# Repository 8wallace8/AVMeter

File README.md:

"# AVMeter"

Versiion 1.2 fixes input order for LM6105.  Also adds negative voltage supply directly from PSU's board.

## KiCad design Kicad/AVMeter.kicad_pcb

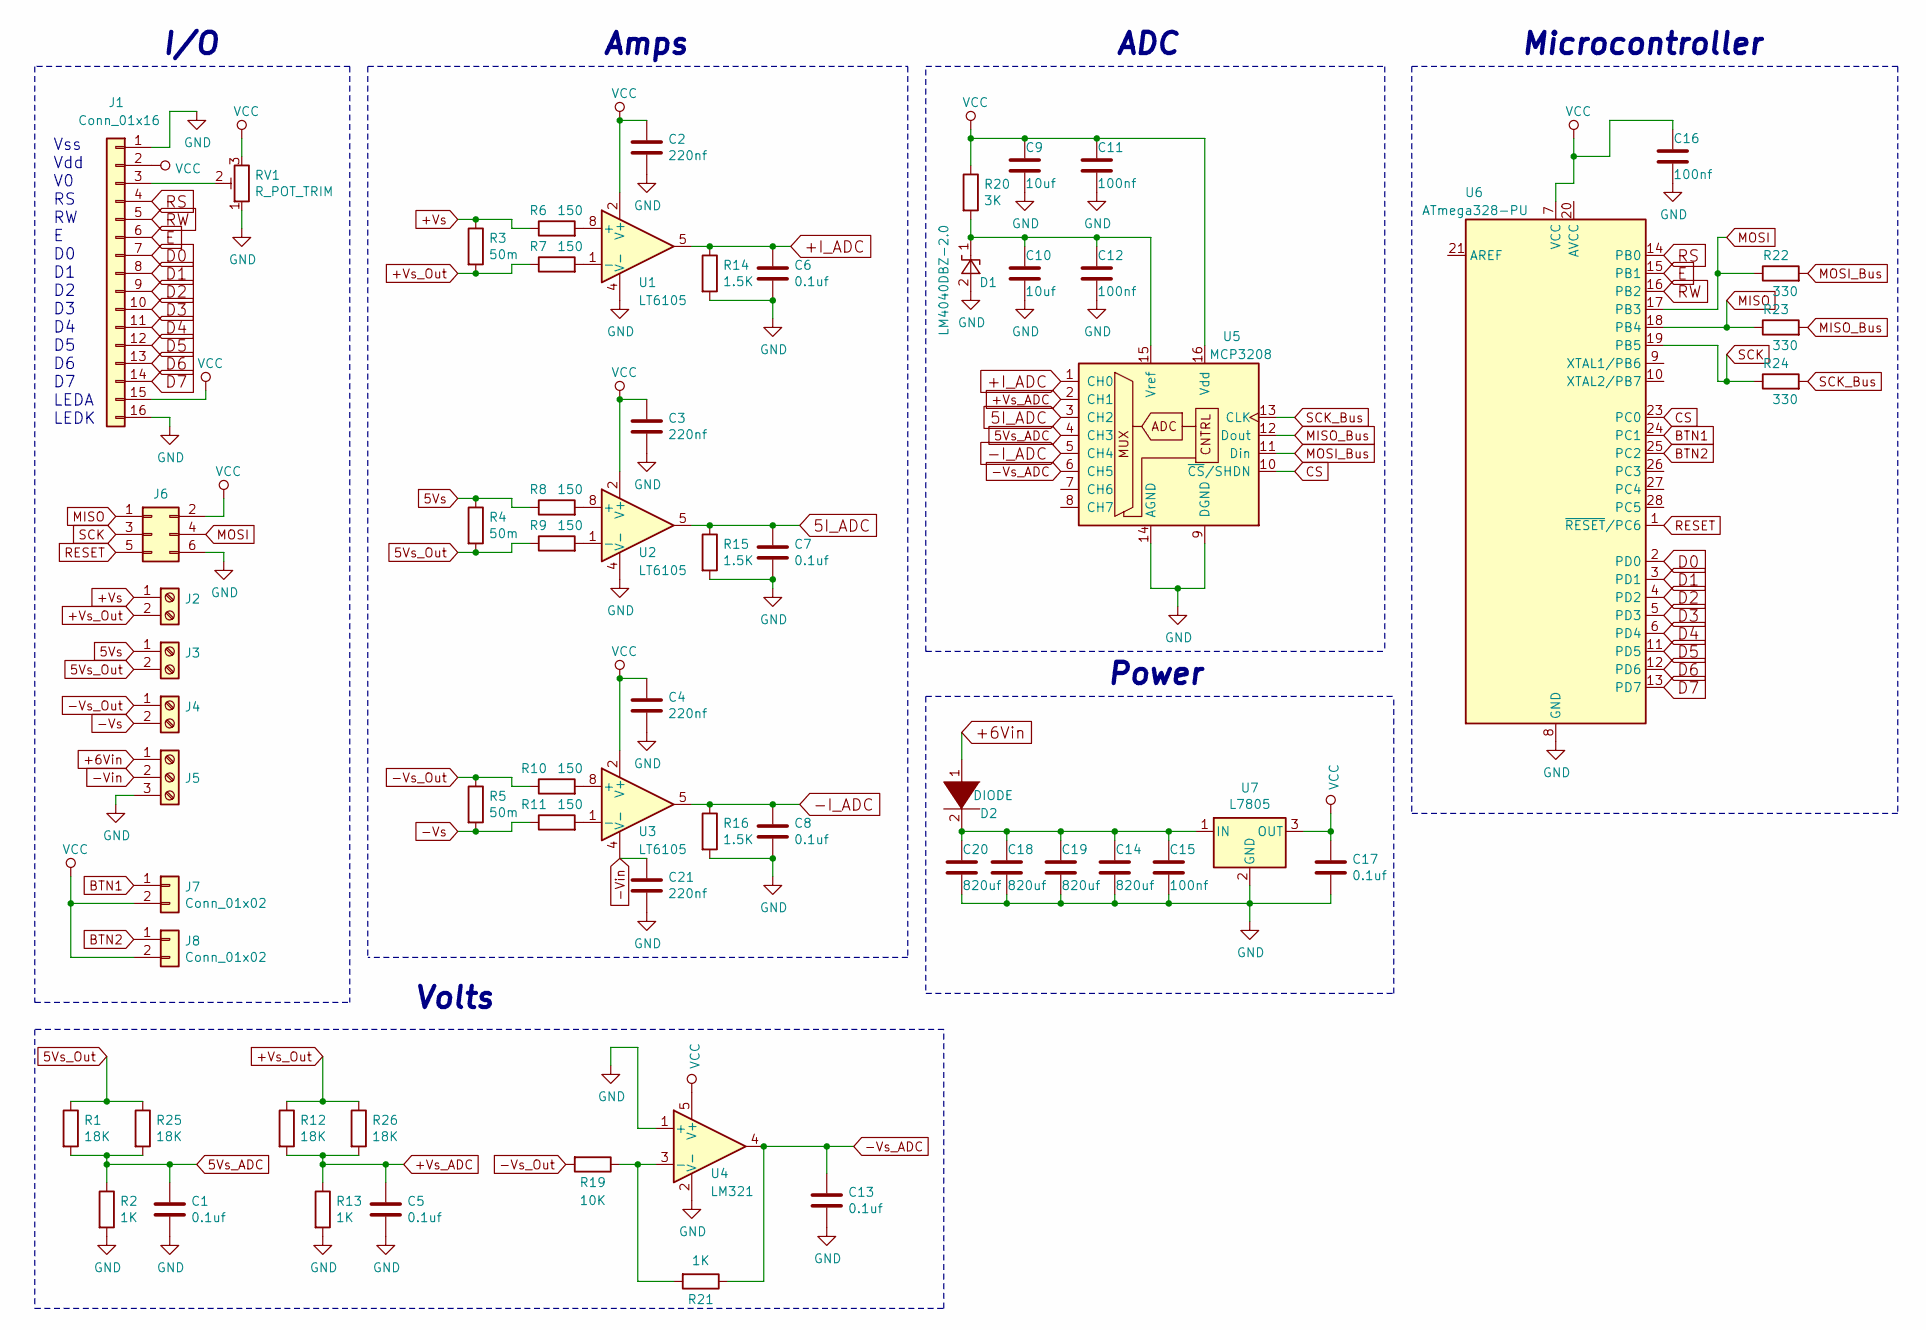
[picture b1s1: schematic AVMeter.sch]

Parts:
C1, C5, C6, C7, C8, C13, C17: 0.1uf; C_1206_3216Metric_Pad1.42x1.75mm_HandSolder
C2, C3, C4, C21: 220nf; C_1206_3216Metric_Pad1.42x1.75mm_HandSolder
C9, C10: 10uf; C_1206_3216Metric_Pad1.42x1.75mm_HandSolder
C11, C12, C15, C16: 100nf; C_1206_3216Metric_Pad1.42x1.75mm_HandSolder
C14, C18, C19, C20: 820uf; CP_Radial_D8.0mm_P3.50mm
D1: LM4040DBZ-2.0; SOT-23
D2: DIODE; D_SOD-123F
J1: Conn_01x16; PinHeader_1x16_P2.54mm_Vertical
J2, J3, J4: Screw_Terminal_01x02; KF301_2Pin_5Pitch
J5: Screw_Terminal_01x03; KF301_3Pin_5Pitch
J6: Conn_02x03_Odd_Even; PinHeader_2x03_P2.54mm_Vertical
J7, J8: Conn_01x02; PinSocket_1x02_P2.54mm_Vertical
R1, R12, R25, R26: 18K; R_1206_3216Metric_Pad1.42x1.75mm_HandSolder
R2, R13, R21: 1K; R_1206_3216Metric_Pad1.42x1.75mm_HandSolder
R3, R4, R5: 50m; R_0612_1632Metric_Pad1.18x3.40mm_HandSolder
R6, R7, R8, R9, R10, R11: 150; R_1206_3216Metric_Pad1.42x1.75mm_HandSolder
R14, R15, R16: 1.5K; R_1206_3216Metric_Pad1.42x1.75mm_HandSolder
R19: 10K; R_1206_3216Metric_Pad1.42x1.75mm_HandSolder
R20: 3K; R_1206_3216Metric_Pad1.42x1.75mm_HandSolder
R22, R23, R24: 330; R_1206_3216Metric_Pad1.42x1.75mm_HandSolder
RV1: R_POT_TRIM; PinHeader_1x03_P2.54mm_Vertical
U1, U2, U3: LT6105; MSOP-8_3x3mm_P0.65mm
U4: LM321; SOT-23-5
U5: MCP3208; SOIC-16_3.9x9.9mm_P1.27mm
U6: ATmega328-PU; DIP-28_W7.62mm
U7: L7805; L7805CDT-TR-DPAK

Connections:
5I_ADC: C7.1, R15.1, U2.5, U5.3 (CH2)
5Vs: J3.1, R4.1, R8.1
5Vs_ADC: C1.1, R1.2, R2.1, R25.2, U5.4 (CH3)
5Vs_Out: J3.2, R1.1, R4.2, R9.1, R25.1
+6Vin: D2.1 (K), J5.1
+I_ADC: C6.1, R14.1, U1.5, U5.1 (CH0)
+Vs: J2.1, R3.1, R6.1
+Vs_ADC: C5.1, R12.2, R13.1, R26.2, U5.2 (CH1)
+Vs_Out: J2.2, R3.2, R7.1, R12.1, R26.1
-I_ADC: C8.1, R16.1, U3.5, U5.5 (CH4)
-Vin: C21.1, J5.2, U3.4 (V-)
-Vs: J4.2, R5.2, R11.1
-Vs_ADC: C13.1, R21.1, U4.4, U5.6 (CH5)
-Vs_Out: J4.1, R5.1, R10.1, R19.2
BTN1: J7.1, U6.24 (PC1)
BTN2: J8.1, U6.25 (PC2)
CS: U5.10 (~CS~/SHDN), U6.23 (PC0)
D0: J1.7, U6.2 (PD0)
D1: J1.8, U6.3 (PD1)
D2: J1.9, U6.4 (PD2)
D3: J1.10, U6.5 (PD3)
D4: J1.11, U6.6 (PD4)
D5: J1.12, U6.11 (PD5)
D6: J1.13, U6.12 (PD6)
D7: J1.14, U6.13 (PD7)
E: J1.6, U6.15 (PB1)
GND: C1.2, C2.2, C3.2, C4.2, C5.2, C6.2, C7.2, C8.2, C9.2, C10.2, C11.2, C12.2, C13.2, C14.2, C15.2, C16.2, C17.2, C18.2, C19.2, C20.2, C21.2, D1.2 (A), J1.1, J1.16, J5.3, J6.6, R2.2, R13.2, R14.2, R15.2, R16.2, RV1.1, U1.4 (V-), U2.4 (V-), U4.1 (+), U4.2 (V-), U5.9 (DGND), U5.14 (AGND), U6.8 (GND), U6.22 (GND), U7.2 (GND)
MISO: J6.1, R23.1, U6.18 (PB4)
MISO_Bus: R23.2, U5.12 (Dout)
MOSI: J6.4, R22.1, U6.17 (PB3)
MOSI_Bus: R22.2, U5.11 (Din)
unnamed: C10.1, C12.1, D1.1 (K), R20.2, U5.15 (Vref)
unnamed: C14.1, C15.1, C18.1, C19.1, C20.1, D2.2 (A), U7.1 (IN)
unnamed: J1.3, RV1.2
unnamed: R6.2, U1.8 (+)
unnamed: R7.2, U1.1 (-)
unnamed: R8.2, U2.8 (+)
unnamed: R9.2, U2.1 (-)
unnamed: R10.2, U3.8 (+)
unnamed: R11.2, U3.1 (-)
unnamed: R19.1, R21.2, U4.3 (-)
RESET: J6.5, U6.1 (~RESET~/PC6)
RS: J1.4, U6.14 (PB0)
RW: J1.5, U6.16 (PB2)
SCK: J6.3, R24.1, U6.19 (PB5)
SCK_Bus: R24.2, U5.13 (CLK)
VCC: C2.1, C3.1, C4.1, C9.1, C11.1, C16.1, C17.1, J1.2, J1.15, J6.2, J7.2, J8.2, R20.1, RV1.3, U1.2 (V+), U2.2 (V+), U3.2 (V+), U4.5 (V+), U5.16 (Vdd), U6.7 (VCC), U7.3 (OUT)

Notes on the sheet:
Vss Vdd V0 RS RW E D0 D1 D2 D3 D4 D5 D6 D7 LEDA LEDK
I/O
Amps
ADC
Microcontroller
Power
Volts

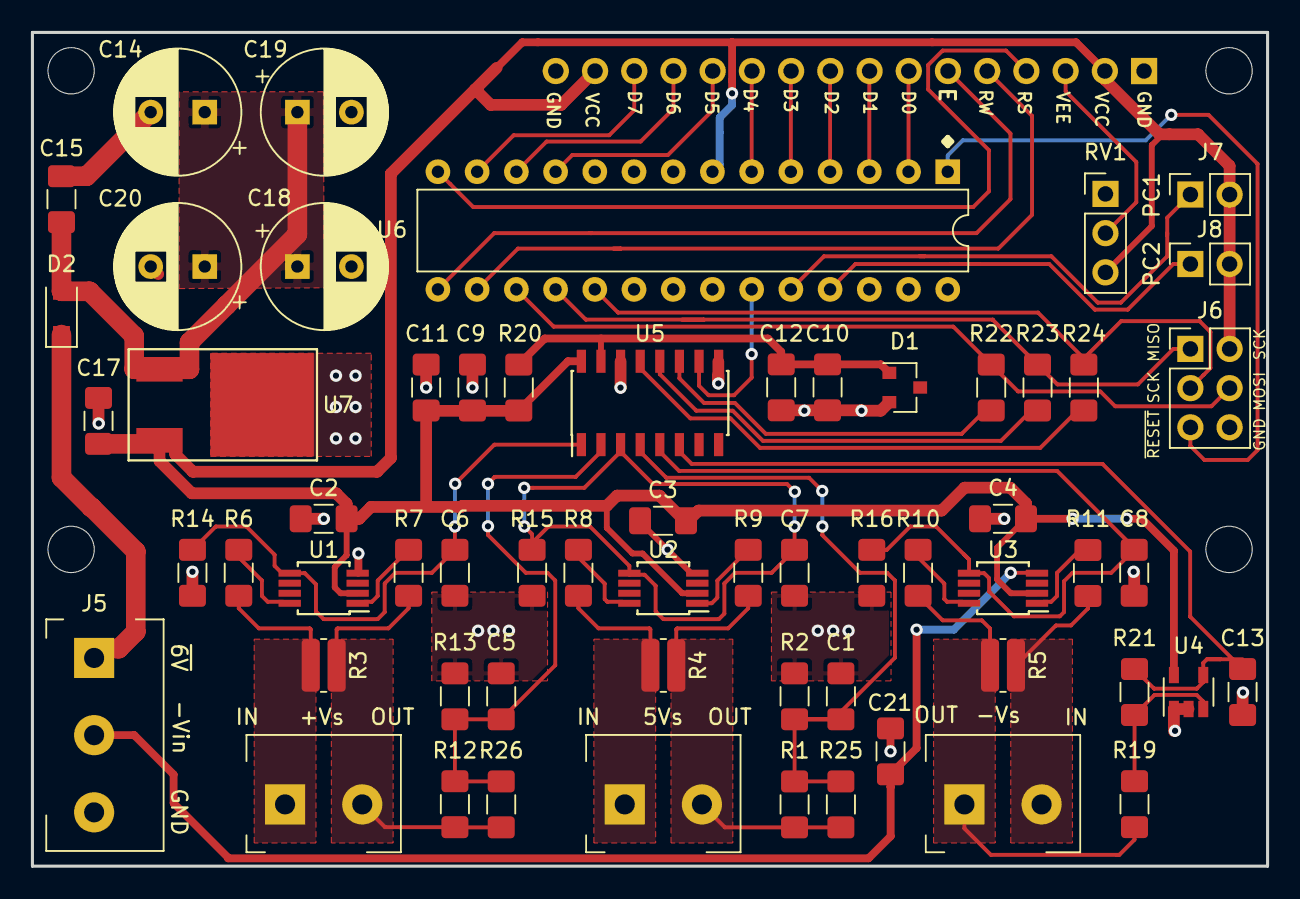
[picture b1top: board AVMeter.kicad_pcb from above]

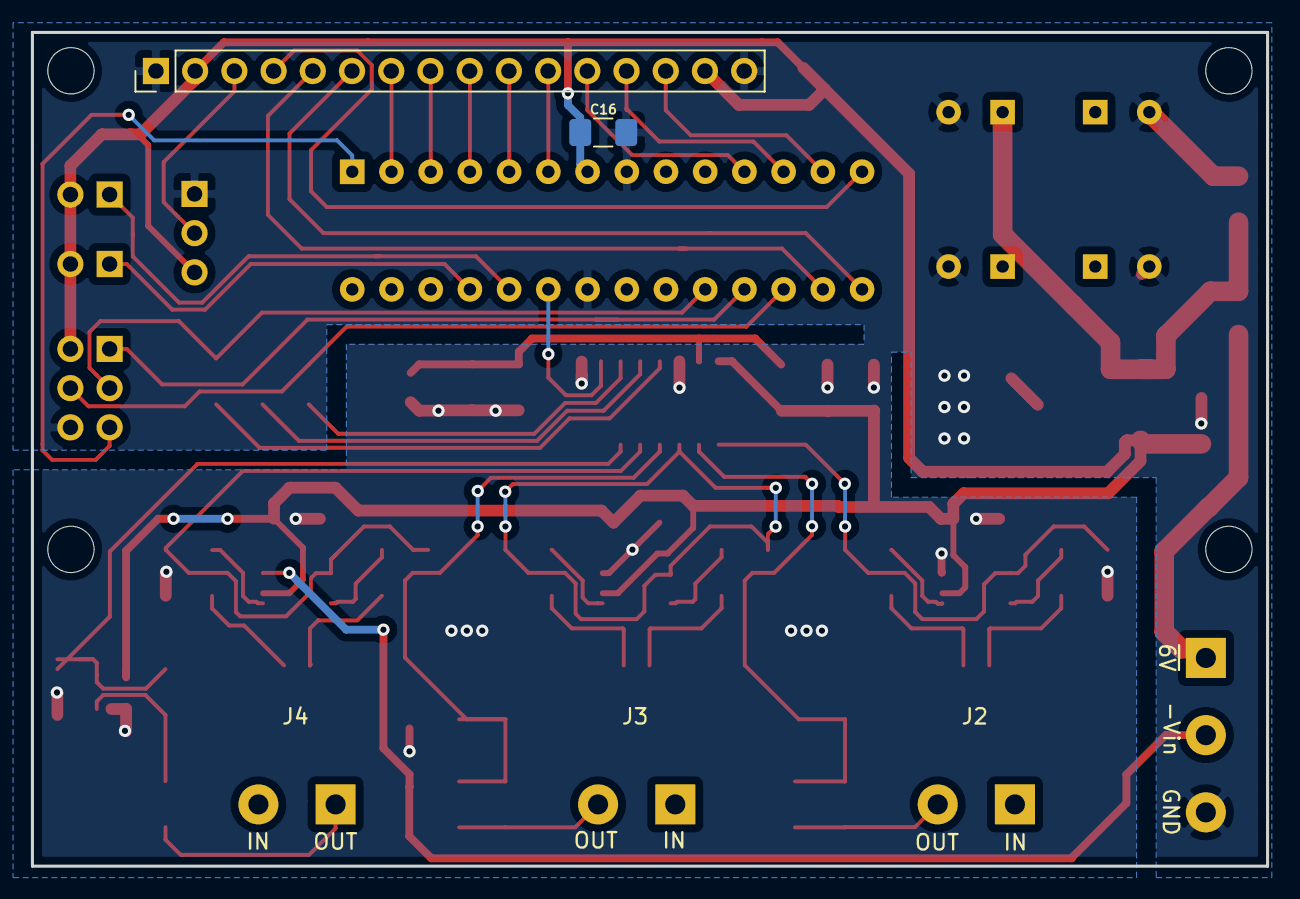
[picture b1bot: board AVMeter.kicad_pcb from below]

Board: 2 copper layers, 80.0 x 54.0 mm, 63 parts (2 on the bottom side), 47 nets.

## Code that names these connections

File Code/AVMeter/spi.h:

/*
 * spi.h
 *
 * Created: 2/3/2019 3:06:21 PM
 *  Author: dkyle
 */ 


#include <avr/io.h>

#ifndef spi
#define spi

//SPI PIN CONFIGURATIONS
#define SPI_PORT 	PORTB
#define SPI_DDR 	DDRB

//PINS
#define SCK_POS 	PB5
#define MISO_POS 	PB4
#define MOSI_POS	PB3



//CS : Chip Select
#define CS_PORT PORTC
#define CS_DDR	DDRC
#define CS_POS PC0

#define CS_HIGH() CS_PORT|=(1<<CS_POS)
#define CS_LOW() CS_PORT&=(~(1<<CS_POS))


void SPIInit();
void SPIClose();
uint8_t SPIWrite(uint8_t data);


/********************************************************************

Function To Initialize the Internal SPI Hardware

********************************************************************/
void SPIInit()
{
	//Set up SPI I/O Ports
	SPI_DDR|=((1<<MOSI_POS)|(1<<SCK_POS));

	//Chip Select PIN is initialize as HIGH i.e. Idle
	//CS PIN is always Active Low (inverted)
	CS_DDR|=(1<<CS_POS);
	CS_HIGH();

	/*

	SPI BUS CONFIGURATION
	---------------------
	*Master Mode
	*MSB first
	*CPOL=0
	*CPHA=0
	*Above two implies SPI MODE0
	*SCK Freq = FCPU/16 i.e. 1MHz

	*/

	SPCR|=(1<<SPE)|(1<<MSTR)|(1<<SPR0);
}



/********************************************************************

Function To Disable the Internal SPI Hardware

********************************************************************/
void SPIClose()
{
	SPCR&=(~(1<<SPE));
	SPI_DDR&=(~((1<<MOSI_POS)|(1<<SCK_POS)));
}



/********************************************************************

Function for SPI Transaction.

Arguments:
	uint8_t data : Data to write

Return Value
	uint8_t : Data Read from BUS

********************************************************************/
uint8_t SPIWrite(uint8_t data)
{
	/* Start transmission */
	SPDR = data;
	/* Wait for transmission complete */
	while(!(SPSR & (1<<SPIF)));

	return (SPDR);
}

#endif

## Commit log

2019-04-28 second commit
2019-04-29 updating ...
2019-05-03 just commiting
2019-08-11 fix for LM6105
2019-08-12 added mount holes and other
2019-08-12 updated sheet info
2019-08-14 release V 1.2
